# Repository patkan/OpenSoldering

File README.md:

OpenSoldering
=============

###Kurzbeschreibung
OpenSource Lötstation mit (hoffentlich mal) Unterstützung für verschiedene JBC-, Weller- und Ersa-Lötkolben

###Aufbau
Modular. Kommunikation über RS485 mit dem SB9-Bussystem

###Ziel
eine OpenSource Lötstation mit Basisstation und einzelnen Satellitenstationen, die jeweils ein Lötgerät (Kolben, Zange, Pinzette) ansteuern. Auch geeignet für Gruppen oder Werkstätten, die mehrere Lötplätze brauchen.

###Status Quo
- Modul für den JBC-Lötkolben T245A in Entwicklung.
- Thermospannung im Arbeitspunkt für C245 Kartusche 4,2mV; Aufnahme der Kennlinie fehlt noch.

###TODOs
- Aufbau und ausführliche Tests am Lötkolben, Programmierung der PI-Regelung mit Vorsteuerung, (vermutlich kein PID-Konzept nötig) und Bau der Kontrollstation.
- Planung für ein Weller-Modul für die modernen Lötspitzen des WXMP-Lötkolbens, die einen einfachen und günstigen Lötkolben versprechen.
- Planung der Kontrollstation:
	* Display: OLED? gLCD?
	* Eingabe: Drehknopf? Touchscreen?
	* zusätzliche Konnektivität: IoT? Bluetooth? Lötrauchabsaugung?
	* Reglerprofile: Optimierung auf Ausregelzeit/minimale Überschwingung?

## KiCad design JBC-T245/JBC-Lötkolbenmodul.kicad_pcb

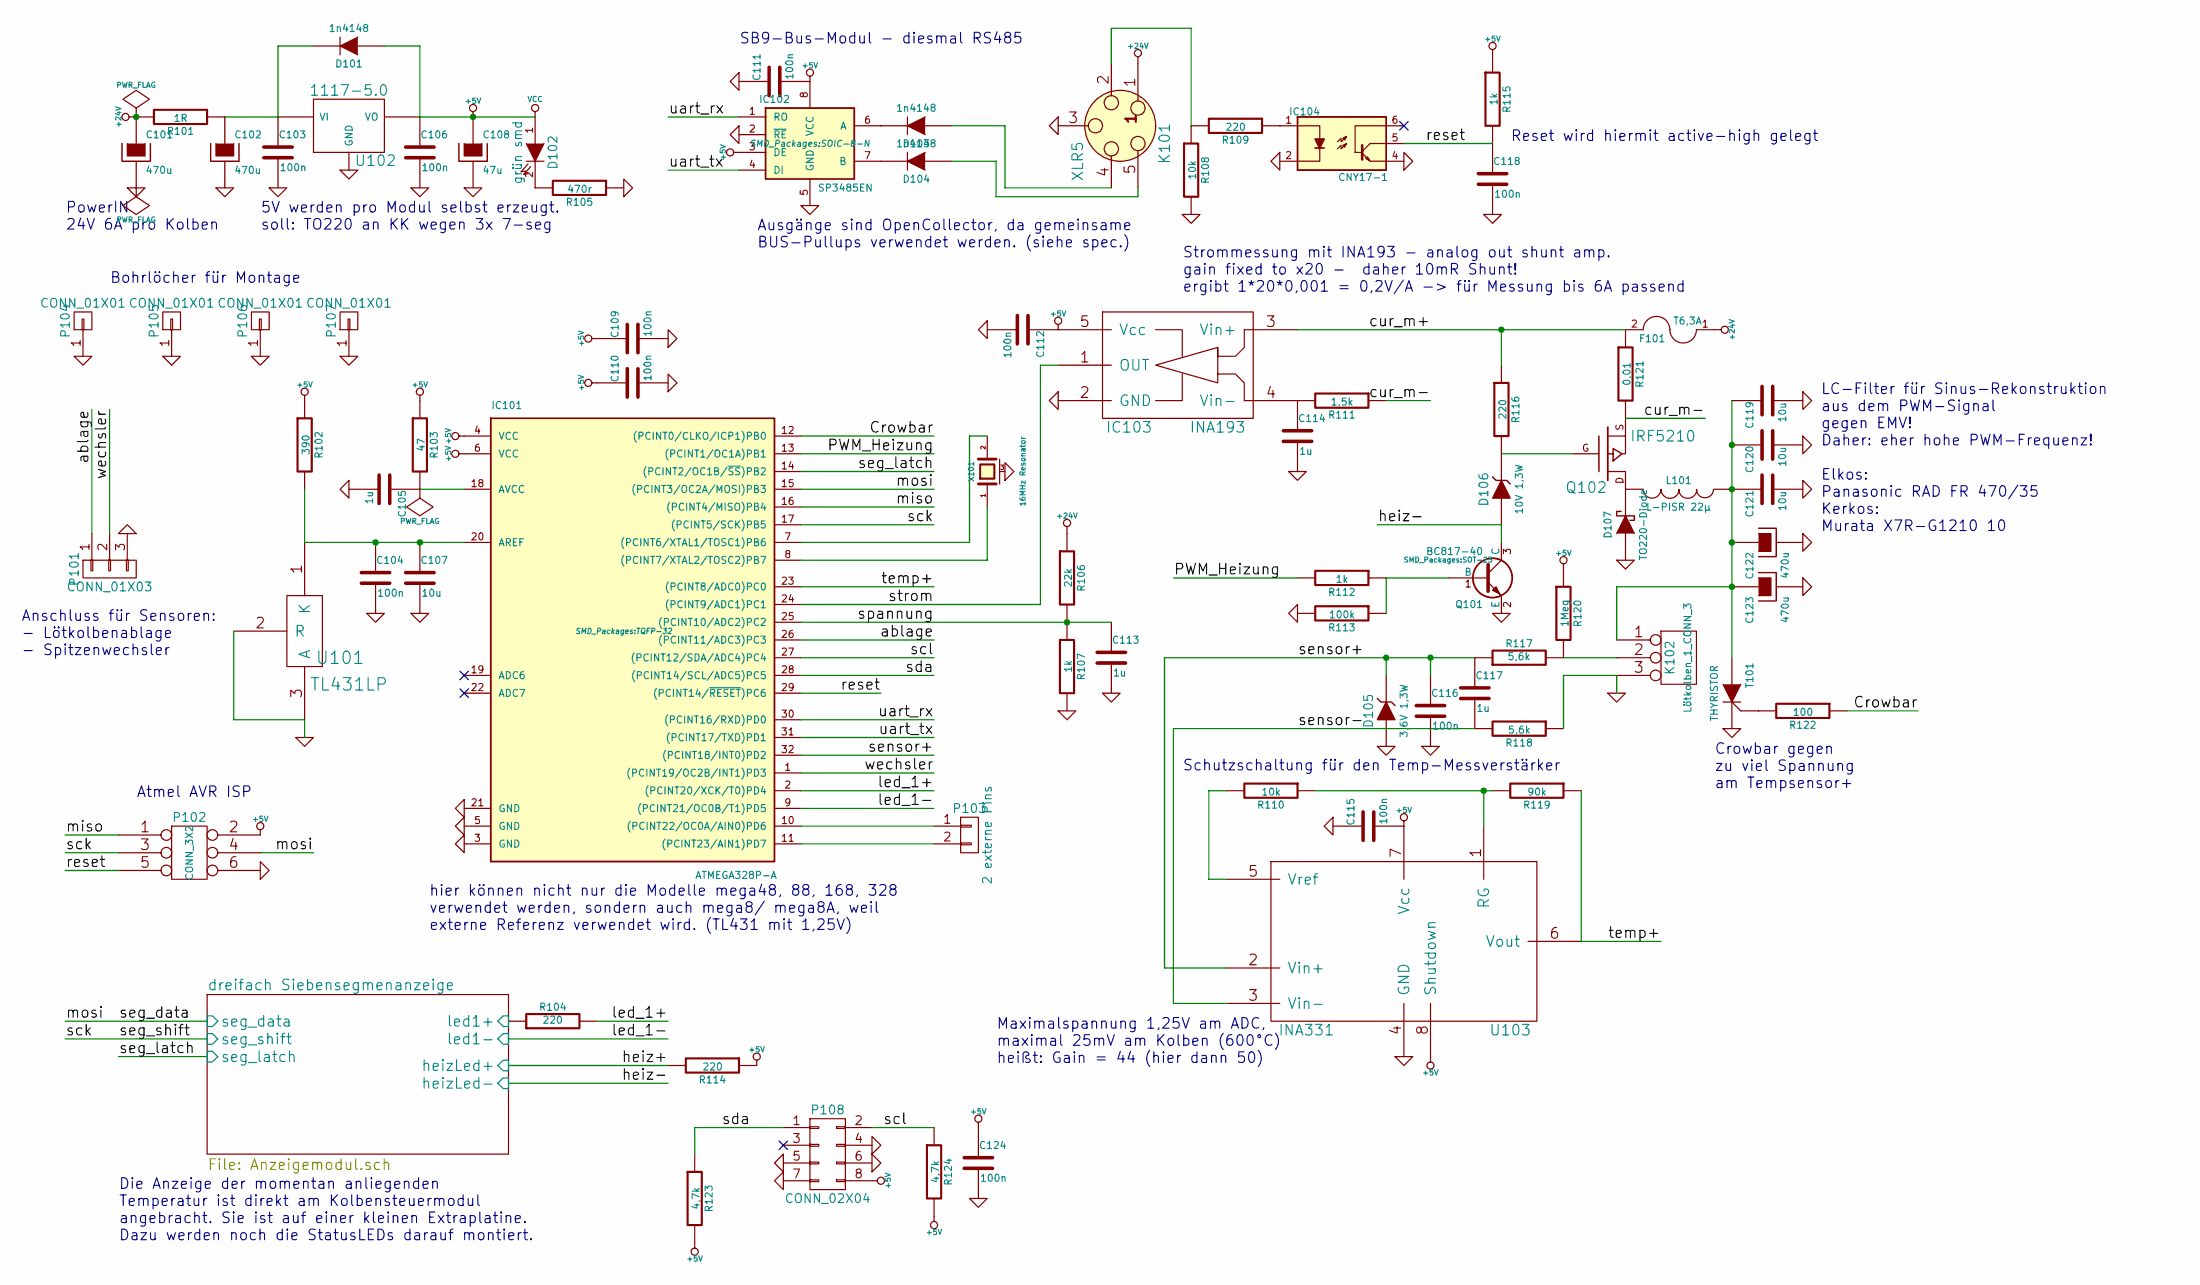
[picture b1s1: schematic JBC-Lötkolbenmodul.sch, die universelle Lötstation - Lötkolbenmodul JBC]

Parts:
C101, C102, C122, C123: 470u; Elko_vert_DM8_RM3-5_CopperClear
C103, C104, C106, C109, C110, C111, C112, C115, C116, C118, C124: 100n; C_0805
C105, C113, C114, C117: 1u; C_0805
C107: 10u; C_0805
C108: 47u; C_1210
C119, C120, C121: 10u; C_1210
D101, D103, D104: 1n4148; Diode-MiniMELF_Standard
D102: grün smd; LED-0805
D105: 3,6V 1,3W; Diode_DO-41_SOD81_Horizontal_RM10
D106: 10V 1,3W; Diode_DO-41_SOD81_Horizontal_RM10
D107: TO220-Diode; TO-220_Neutral123_Vertical
F101: T6,3A; Fuseholder5x20_Horizontal_closed_Bulgin_FX0457
IC101: ATMEGA328P-A; TQFP-32
IC102: SP3485EN; SOIC-8-N
IC103: INA193; SOT-23-5
IC104: CNY17-1; DIP-6__300_ELL
K101: XLR5; Pin_Header_Straight_1x05
K102: Lötkolben_1_CONN_3; Pin_Header_Straight_1x03
L101: L-PISR 22µ; L_Fastron_PISR
P101: CONN_01X03; Pin_Header_Straight_1x03
P102: CONN_3X2; Pin_Header_Straight_2x03
P103: 2 externe Pins; Pin_Header_Straight_1x02
P104, P105, P106, P107: CONN_01X01; 1pin
P108: CONN_02X04; SOIC-8-N
Q101: BC817-40; SOT-23
Q102: IRF5210; DPAK-3_GDS
R101: 1R; R_0603
R102: 390; R_0603
R103: 47; R_0603
R104, R109, R114, R116: 220; R_0603
R105: 470r; R_0603
R106: 22k; R_0603
R107, R112, R115: 1k; R_0603
R108, R110: 10k; R_0603
R111: 1,5k; R_0603
R113: 100k; R_0603
R117, R118: 5,6k; R_0603
R119: 90k; R_0603
R120: 1Meg; R_0603
R121: 0,01; R_1210
R122: 100; R_0603
R123, R124: 4,7k; R_0603
T101: THYRISTOR; TO-220_Neutral123_Vertical
U101: TL431LP; SOIC-8-N
U102: 1117-5.0; TO-220_Neutral123_Vertical
U103: INA331; SSOP-8
X101: 16MHz Resonator; CerOsc_3,2x1,3

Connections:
+24V: C101.1, F101.1, K101.1, R101.2, R106.1
/Crowbar: IC101.12 ((PCINT0/CLKO/ICP1)PB0), R122.1
/PWM_Heizung: IC101.13 ((PCINT1/OC1A)PB1), R112.2
/ablage: IC101.26 ((PCINT11/ADC3)PC3), P101.1
/cur_m+: F101.2, IC103.3 (Vin+), R116.1, R121.1
/cur_m-: Q102.S, R111.1, R121.2
/dreifach Siebensegmenanzeige/heizLed+: R114.2; also elsewhere on the board
/dreifach Siebensegmenanzeige/heizLed-: D106.1 (A), Q101.3 (C); also elsewhere on the board
/dreifach Siebensegmenanzeige/led1+: R104.1; also elsewhere on the board
/dreifach Siebensegmenanzeige/led1-: IC101.9 ((PCINT21/OC0B/T1)PD5); also elsewhere on the board
/dreifach Siebensegmenanzeige/seg_data: IC101.15 ((PCINT3/OC2A/MOSI)PB3), P102.4; also elsewhere on the board
/dreifach Siebensegmenanzeige/seg_latch: IC101.14 ((PCINT2/OC1B/~SS~)PB2); also elsewhere on the board
/dreifach Siebensegmenanzeige/seg_shift: IC101.17 ((PCINT5/SCK)PB5), P102.3; also elsewhere on the board
/led_1+: IC101.2 ((PCINT20/XCK/T0)PD4), R104.2
/miso: IC101.16 ((PCINT4/MISO)PB4), P102.1
/reset: C118.1, IC101.29 ((PCINT14/~RESET~)PC6), IC104.5, P102.5, R115.2
/scl: IC101.27 ((PCINT12/SDA/ADC4)PC4), P108.2, R124.1
/sda: IC101.28 ((PCINT14/SCL/ADC5)PC5), P108.1, R123.1
/sensor+: C116.1, C117.1, D105.2 (K), IC101.32 ((PCINT18/INT0)PD2), R117.1, U103.2 (Vin+)
/sensor-: C117.2, R118.2, U103.3 (Vin-)
/spannung: C113.1, IC101.25 ((PCINT10/ADC2)PC2), R106.2, R107.1
/strom: IC101.24 ((PCINT9/ADC1)PC1), IC103.1 (OUT)
/temp+: IC101.23 ((PCINT8/ADC0)PC0), R119.1, U103.6 (Vout)
/uart_rx: IC101.30 ((PCINT16/RXD)PD0), IC102.1 (RO)
/uart_tx: IC101.31 ((PCINT17/TXD)PD1), IC102.4 (DI)
/wechsler: IC101.1 ((PCINT19/OC2B/INT1)PD3), P101.2
unnamed: C102.1, C103.1, D101.2 (K), R101.1, U102.VI
unnamed: C104.1, C107.1, IC101.20 (AREF), R102.2, U101.1 (K)
unnamed: C105.1, IC101.18 (AVCC), R103.2
unnamed: C114.1, IC103.4 (Vin-), R111.2
unnamed: C119.1, C120.1, C121.1, C122.1, C123.1, K102.1, L101.1, T101.A
unnamed: D102.2 (K), R105.2
unnamed: D103.1 (A), K101.4 (P3)
unnamed: D103.2 (K), IC102.6 (A)
unnamed: D104.1 (A), K101.5
unnamed: D104.2 (K), IC102.7 (B)
unnamed: D106.2 (K), Q102.G, R116.2
unnamed: D107.2 (K), L101.2, Q102.D
unnamed: IC101.7 ((PCINT6/XTAL1/TOSC1)PB6), X101.2
unnamed: IC101.8 ((PCINT7/XTAL2/TOSC2)PB7), X101.1
unnamed: IC101.10 ((PCINT22/OC0A/AIN0)PD6), P103.1
unnamed: IC101.11 ((PCINT23/AIN1)PD7), P103.2
unnamed: IC104.1, R109.1
unnamed: K101.2, R108.1, R109.2
unnamed: K102.2 (PM), R117.2, R120.2
unnamed: Q101.1 (B), R112.1, R113.1
unnamed: R110.1, R119.2, U103.1 (RG)
unnamed: R110.2, U103.5 (Vref)
unnamed: R122.2, T101.G

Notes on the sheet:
Atmel AVR ISP
PowerIN 24V 6A pro Kolben
Crowbar gegen zu viel Spannung am Tempsensor+
Schutzschaltung für den Temp-Messverstärker
SB9-Bus-Modul - diesmal RS485
Ausgänge sind OpenCollector, da gemeinsame BUS-Pullups verwendet werden. (siehe spec.)
5V werden pro Modul selbst erzeugt. soll: TO220 an KK wegen 3x 7-seg
Anschluss für Sensoren: - Lötkolbenablage - Spitzenwechsler
LC-Filter für Sinus-Rekonstruktion aus dem PWM-Signal gegen EMV! Daher: eher hohe PWM-Frequenz! Elkos: Panasonic RAD FR 470/35 Kerkos: Murata X7R-G1210 10
Strommessung mit INA193 - analog out shunt amp. gain fixed to x20 - daher 10mR Shunt! ergibt 1*20*0,001 = 0,2V/A -> für Messung bis 6A passend
Die Anzeige der momentan anliegenden Temperatur ist direkt am Kolbensteuermodul angebracht. Sie ist auf einer kleinen Extraplatine. Dazu werden noch die StatusLEDs darauf montiert.
Maximalspannung 1,25V am ADC, maximal 25mV am Kolben (600°C) heißt: Gain = 44 (hier dann 50)
Reset wird hiermit active-high gelegt
hier können nicht nur die Modelle mega48, 88, 168, 328 verwendet werden, sondern auch mega8/ mega8A, weil externe Referenz verwendet wird. (TL431 mit 1,25V)
Bohrlöcher für Montage

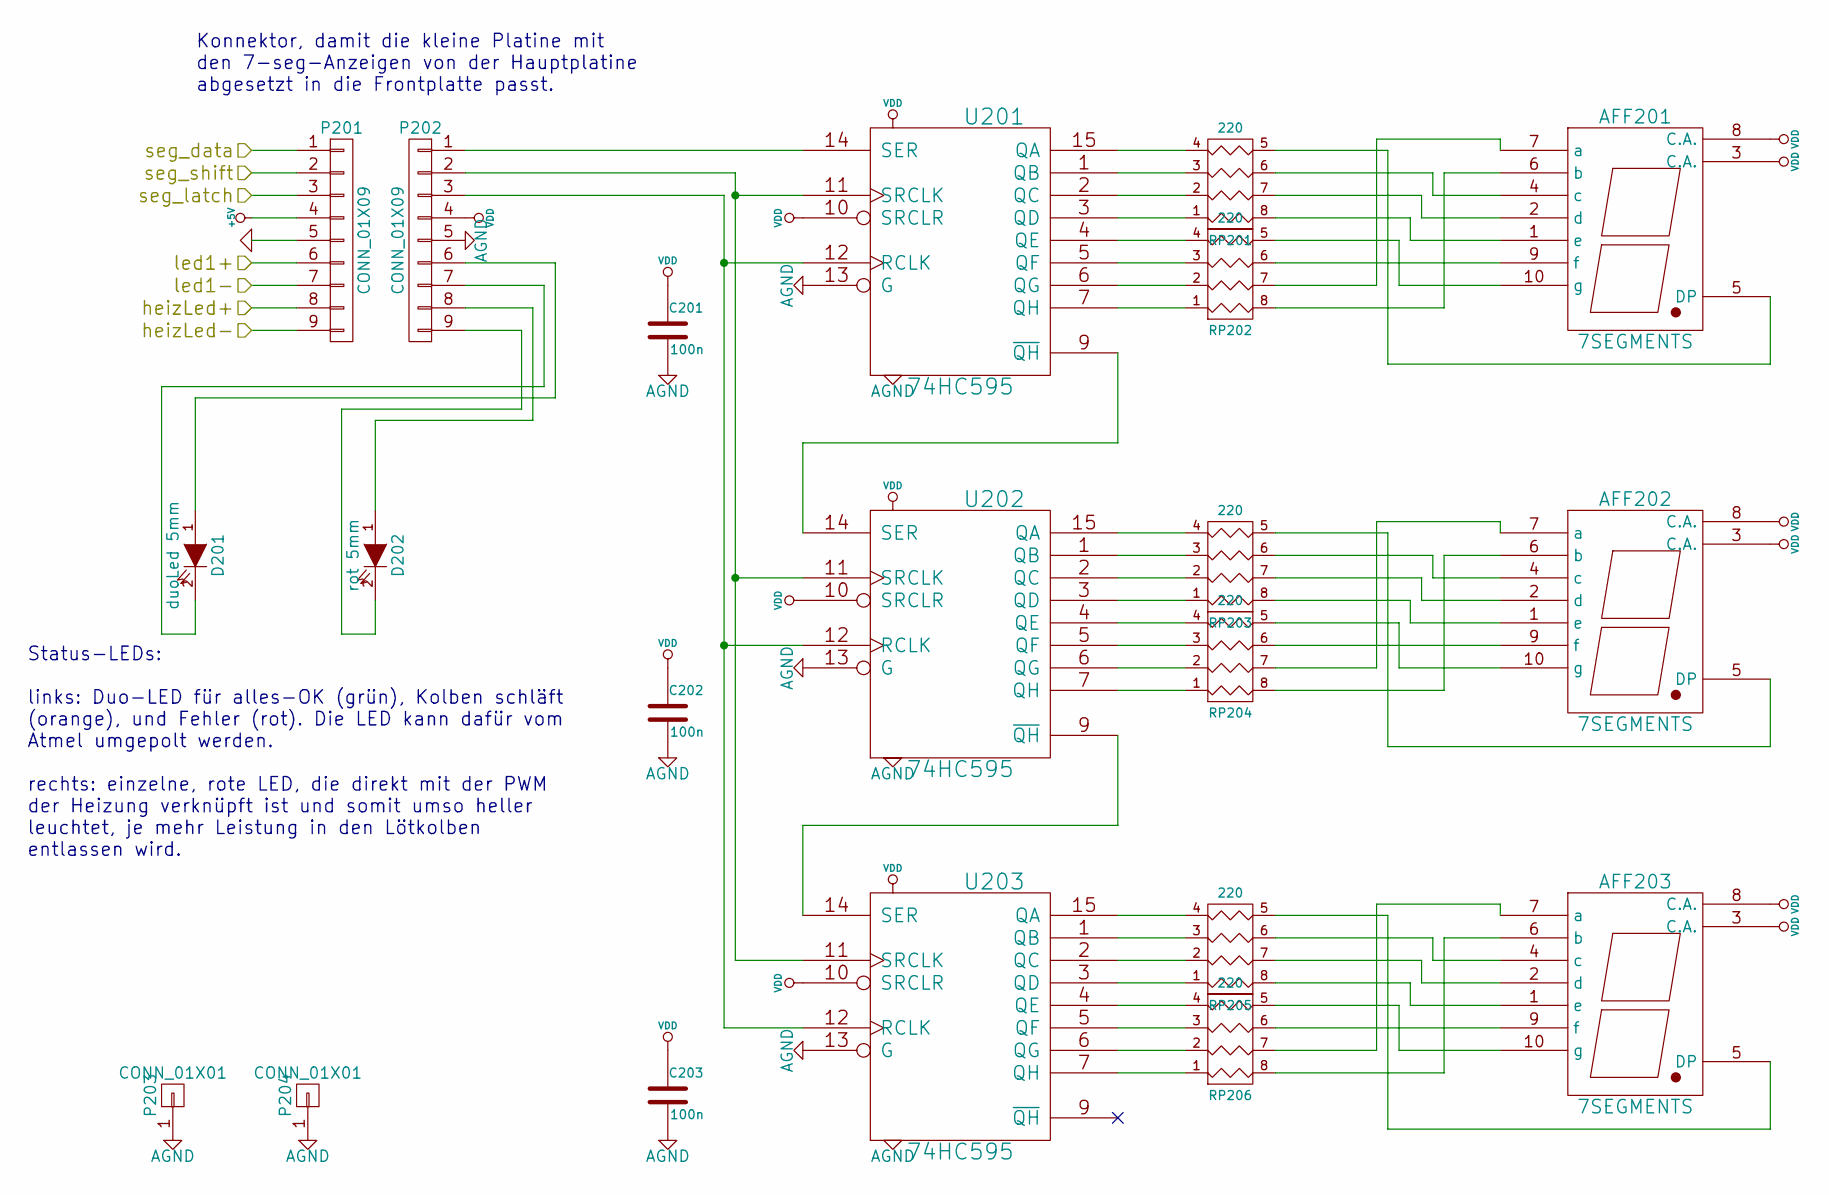
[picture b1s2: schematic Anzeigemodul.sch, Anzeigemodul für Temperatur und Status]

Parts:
AFF201, AFF202, AFF203: 7SEGMENTS; DIP-10__300_ELL
C201, C202, C203: 100n; C_0805
D201: duoLed 5mm; LED-5MM
D202: rot 5mm; LED-5MM
P201: CONN_01X09; Pin_Header_Straight_1x09
P202: CONN_01X09; Pin_Header_Angled_1x09
P203, P204: CONN_01X01; 1pin
RP201, RP202, RP203, RP204, RP205, RP206: 220; R_Cat16-4
U201, U202, U203: 74HC595; SO-16-N

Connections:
/dreifach Siebensegmenanzeige/heizLed+: P201.8; also elsewhere on the board
/dreifach Siebensegmenanzeige/heizLed-: P201.9; also elsewhere on the board
/dreifach Siebensegmenanzeige/led1+: P201.6; also elsewhere on the board
/dreifach Siebensegmenanzeige/led1-: P201.7; also elsewhere on the board
/dreifach Siebensegmenanzeige/seg_data: P201.1; also elsewhere on the board
/dreifach Siebensegmenanzeige/seg_latch: P201.3; also elsewhere on the board
/dreifach Siebensegmenanzeige/seg_shift: P201.2; also elsewhere on the board
unnamed: AFF201.1 (e), RP201.8 (R1)
unnamed: AFF201.2 (d), RP201.7 (R2)
unnamed: AFF201.4 (c), RP201.6 (R3)
unnamed: AFF201.5 (DP), RP201.5 (R4)
unnamed: AFF201.6 (b), RP202.8 (R1)
unnamed: AFF201.7 (a), RP202.7 (R2)
unnamed: AFF201.9 (f), RP202.6 (R3)
unnamed: AFF201.10 (g), RP202.5 (R4)
unnamed: AFF202.1 (e), RP203.8 (R1)
unnamed: AFF202.2 (d), RP203.7 (R2)
unnamed: AFF202.4 (c), RP203.6 (R3)
unnamed: AFF202.5 (DP), RP203.5 (R4)
unnamed: AFF202.6 (b), RP204.8 (R1)
unnamed: AFF202.7 (a), RP204.7 (R2)
unnamed: AFF202.9 (f), RP204.6 (R3)
unnamed: AFF202.10 (g), RP204.5 (R4)
unnamed: AFF203.1 (e), RP205.8 (R1)
unnamed: AFF203.2 (d), RP205.7 (R2)
unnamed: AFF203.4 (c), RP205.6 (R3)
unnamed: AFF203.5 (DP), RP205.5 (R4)
unnamed: AFF203.6 (b), RP206.8 (R1)
unnamed: AFF203.7 (a), RP206.7 (R2)
unnamed: AFF203.9 (f), RP206.6 (R3)
unnamed: AFF203.10 (g), RP206.5 (R4)
unnamed: D201.1 (A), P202.6
unnamed: D201.2 (K), P202.7
unnamed: D202.1 (A), P202.8
unnamed: D202.2 (K), P202.9
unnamed: P202.1, U201.14 (SER)
unnamed: P202.2, U201.11 (SRCLK), U202.11 (SRCLK), U203.11 (SRCLK)
unnamed: P202.3, U201.12 (RCLK), U202.12 (RCLK), U203.12 (RCLK)
unnamed: RP201.1, U201.3 (QD)
unnamed: RP201.2, U201.2 (QC)
unnamed: RP201.3, U201.1 (QB)
unnamed: RP201.4, U201.15 (QA)
unnamed: RP202.1, U201.7 (QH)
unnamed: RP202.2, U201.6 (QG)
unnamed: RP202.3, U201.5 (QF)
unnamed: RP202.4, U201.4 (QE)
unnamed: RP203.1, U202.3 (QD)
unnamed: RP203.2, U202.2 (QC)
unnamed: RP203.3, U202.1 (QB)
unnamed: RP203.4, U202.15 (QA)
unnamed: RP204.1, U202.7 (QH)
unnamed: RP204.2, U202.6 (QG)
unnamed: RP204.3, U202.5 (QF)
unnamed: RP204.4, U202.4 (QE)
unnamed: RP205.1, U203.3 (QD)
unnamed: RP205.2, U203.2 (QC)
unnamed: RP205.3, U203.1 (QB)
unnamed: RP205.4, U203.15 (QA)
unnamed: RP206.1, U203.7 (QH)
unnamed: RP206.2, U203.6 (QG)
unnamed: RP206.3, U203.5 (QF)
unnamed: RP206.4, U203.4 (QE)
unnamed: U201.9 (~QH), U202.14 (SER)
unnamed: U202.9 (~QH), U203.14 (SER)

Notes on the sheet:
Konnektor, damit die kleine Platine mit den 7-seg-Anzeigen von der Hauptplatine abgesetzt in die Frontplatte passt.
Status-LEDs: links: Duo-LED für alles-OK (grün), Kolben schläft (orange), und Fehler (rot). Die LED kann dafür vom Atmel umgepolt werden. rechts: einzelne, rote LED, die direkt mit der PWM der Heizung verknüpft ist und somit umso heller leuchtet, je mehr Leistung in den Lötkolben entlassen wird.

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
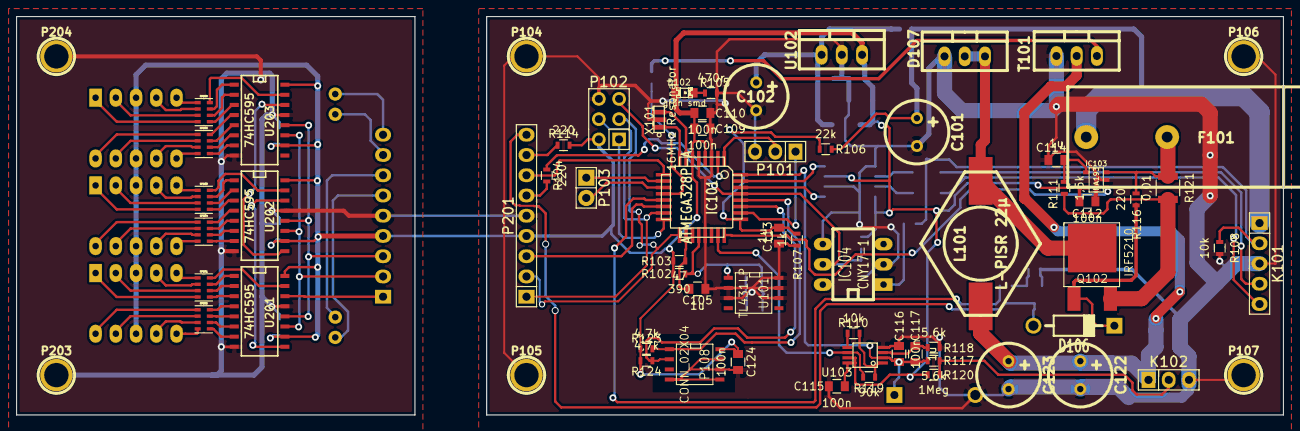
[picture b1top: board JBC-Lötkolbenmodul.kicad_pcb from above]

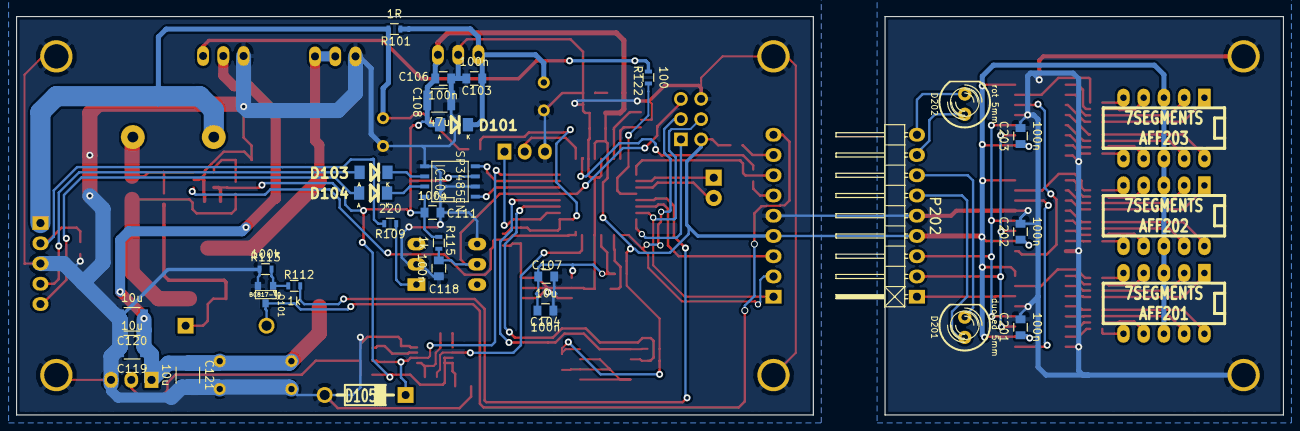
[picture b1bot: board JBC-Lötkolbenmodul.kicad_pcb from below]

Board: 2 copper layers, 159.0 x 50.0 mm, 99 parts (31 on the bottom side), 108 nets.

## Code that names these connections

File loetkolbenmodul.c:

/*
 *    Filename: loetkobenmodul.c
 *     Version: 0.0.4
 * Description: Ansteuerung eines JBC T245A Lötkolbens
 *     License: GPLv3 or later
 *     Depends: global.h, io.h, interrupt.h, sb9, i2c
 *
 *      Author: Copyright (C) Philipp Hörauf
 *        Date: 2014-12-19
 *
 *  This program is free software; you can redistribute it and/or modify
 *  it under the terms of the GNU General Public License as published by
 *  the Free Software Foundation; either version 2 of the License, or
 *  (at your option) any later version.
 *
 *  This program is distributed in the hope that it will be useful,
 *  but WITHOUT ANY WARRANTY; without even the implied warranty of
 *  MERCHANTABILITY or FITNESS FOR A PARTICULAR PURPOSE.  See the
 *  GNU General Public License for more details.
 *
 *  You should have received a copy of the GNU General Public License
 *  along with this program; if not, write to the Free Software
 *  Foundation, Inc., 59 Temple Place, Suite 330, Boston, MA  02111-1307  USA
 *
 */

#include "definitionen.h"
#include "pid.c"
extern volatile float kp, ki, kd; //TODO --> das hier soll noch weg


void setKolbenPower (float sollwert) {
	// 16bit Timer1 auf FastPWM, Ausgang OC1A sei Lötkolben.
}

// Der ADC wird interruptgesteuert
volatile uint8_t counter = 0; // für Berechnung von Heizleistung und Temperatur des Lötkolbens
volatile float leistung = 0, rawtemp = 0, spitzentemp = 0;
volatile uint16_t heizstrom = 0, eingangsspannung = 0; // U in mV, I in mA
volatile uint16_t solltemperatur = 0, platinentemperatur = 0;

//volatile float ki = 1, kp = 1, kd = 1; // werden bereits in pid.c deklariert --> Zugriff sollte am besten nur über setTunings erfolgen

ISR (TIMER0_OVF_vect, ISR_BLOCK) {
	ADMUX = ADMUX & 0b11100000; // lösche selektiv die MUX-Bits
	ADMUX |= (counter%3); // setze ADC-Kanal neu
	ADCSRA |= 1<<ADSC; // start conversion

	// Auslesung der Temperatur des LM75-Sensors
	static uint8_t i2cAuslesung = 0;
	if (i2cAuslesung == 123) { // es sind ca 500 ms vergangen
		platinentemperatur = (i2cRxLm75 (0b1001000)) /16; // erst mal in ganzen °C
		i2cAuslesung = 0;
	} else {
		i2cAuslesung++;
	}


	// PID Regler muss auch hier drin arbeiten, da er mit gleichem Zeitabstand
	// ausgeführt wird, wie der ADC. bzw. mit 1/3 der ADC Frequenz.

	/* Erklärung der Ausgangsübertragungsfunktion und der Regelung:
	

	* 
	* yk	= Ausgangswert des Integrators
	* ek	= Differenz der Temperatur vom Sollwert (+ => zu kalt)
	* ki	= I-Verstärungswert
	* kr	= Reglerverstärkung
	* 
	* Eine Vorsteuerung hat wegen der stark wechselnden Lastsituationen
	* keinen großen Sinn und wird daher weggelassen.

	*
	* Die Störung Z(s) wirkt direkt auf die Temperatur der Lötspitze ein, sie
	* ist der Wärmestrom von der Lötspitze in die Luft (Standardfall) oder in
	* die Lötstelle (Regler muss eingreifen)
	*/


	//TODO: dies ist der neue Aufruf für die externe PID-Funktion
	//float yk;
	//yk = pid_compute(spitzentemp, solltemperatur);



	
	// Regler (Konzept: PI)
	float ek = solltemperatur - rawtemp;
	static float yk;
	yk += (ki * ek);
	

	// Weitergabe an Ausgabefunktion:
	setKolbenPower (yk + (kp * ek));
}

// ADC Conversion Complete Interrupt
// ADC0 = Temperatur, ADC1 = Heizstrom, ADC2 = Systemspannung
// Die Werte können noch kalibriert werden, allerdings nicht zur Laufzeit.

#define REFERENZ 1			// externe Referenz, 1250mV also 1,2207mV pro STEP
#define ABWEICHUNG 0.220703125		// gemessene Abweichung in %/100 vom exakten Referenzspannungswert
#define MITTELWERTE 4
#define SPANNUNG_PRO_GRAD 1.00000	// Spannung am ADC pro Grad am Lötkolben
#define SPANNUNG_PRO_AMPERE 0.2		// Spannung am ADC pro Ampere das durch die Heizung fließt
#define SPANNUNG_PRO_VOLT 0.04347826	// Spannung am ADC pro Volt der Versorgungsspannung

ISR (ADC_vect, ISR_BLOCK) {
	// 	uartTxStrln("adc");
	// ADC-Auslesungen und Rechnung mit Gleitmittelwert über 4 Werte
	static uint16_t tabelle[3*MITTELWERTE]; // hier kommen die ADC-werte rein.
	uint16_t temp=0;
	tabelle[counter] = ADC; // fülle Tabelle mit ADC-Werten

// 	TODO: Formeln anpassen!!

	switch (counter%3) {
		case 0:
			// Achtung: die Lötspitze wird kaltstellenkompensiert (daher die Zusatzvariable)
			spitzentemp = spitzentemp*0.95 + (((float)((temp*REFERENZ)<<2)*ABWEICHUNG*SPANNUNG_PRO_GRAD) + platinentemperatur)*0.05;
			rawtemp = ((float)((tabelle[counter]*REFERENZ)<<2)*ABWEICHUNG*SPANNUNG_PRO_GRAD) + platinentemperatur;
			break;

		case 1:
			// Heizstrom wird ausgerechnet
			for(uint8_t i=0; i<MITTELWERTE; i++) {
				temp += tabelle[1 + 3*i];
			}
			heizstrom = (uint16_t)((float)((temp*REFERENZ)<<2)*ABWEICHUNG*SPANNUNG_PRO_AMPERE);
			break;

		case 2:
			// Eingangsspannung wird ausgerechnet
			for(uint8_t i=0; i<MITTELWERTE; i++) {
				temp += tabelle[2 + 3*i];
			}
			eingangsspannung = (uint16_t)((float)temp*ABWEICHUNG*SPANNUNG_PRO_VOLT);
			break;
	}
	counter++;
	if (counter == 3*MITTELWERTE) { // setze Counter zurück
		counter = 0;
	}
	leistung = ((float)heizstrom * (float)eingangsspannung) / 1000; // Leistung in Watt
}



int main(void) {

	// Allgemeine PIN- und PORT-Einstellungen
	DDRB = 1<<PB0 | 1<<PB1 | 1<<PB2 | 1<<PB3 | 1<<PB5;
	DDRD = 1<<PD1 | 1<<PD4 | 1<<PD5; // PD4 ist WS2812B Datenpin
	PORTC = 1<<PC3; // Pullup für Lötkolbenständerschalter
	PORTD = 1<<PD3; // Lötspitzenwechslerschalter

	delayms(100);

	spiInit();
	i2cInit();
	lm75Init();
// 	timerInit();
// 	uartInit();
	writeSegments(42);

	// Initialiserung der WS2812-StatusLED
	struct cRGB led[1];
	led[0].g=128;
	led[0].b=75;
	led[0].b=25;
	ws2812_setleds(led,1);

// 	sei(); // und es seien Interrupts :D


	delayus(10);
	i2cRxLm75Start(0b1001000);

	while(1) {
// 		i2cRxLm75Start(0b1001000);
// 		temp = i2cRxLm75 (0b1001000);
// 		writeSegments (i2cERR & 0xF8);
		writeSegments (platinentemperatur);
		delayms(100);
	}
	return 0;
}

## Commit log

2014-10-26 initial commit - erst mal das Projekt so online gestellt. philippH
2014-11-21 schutz für den Temperaturmesswandler verbessert
2014-12-19 Programm angefangen.
2014-12-20 fehlerhaftes footprint des 16MHz resonators. fixed. programm geht los.
2014-12-20 Planung Controllermodul und Thermospannung C245 Kartusche hinzugefügt.
2014-12-20 programm zählt ein bisschen. LED-anzeigen gehen also.
2014-12-20 gerberfiles in der gitignore datei verzeichnet.
2014-12-20 die Modularisierung zieht ein. inits und definitionen werden aus der main-Datei ausgelagert.
2014-12-20 dateien verschoben, da diese nicht spezifisch für den JBC-kolben sind.
2014-12-21 light_ws2812 hinzugefügt
2014-12-21 anfang hardware i2c für den LM75 Tempsensor
2014-12-21 ws2812 port und Pin korrekt eingestellt. i2c geht noch nicht.
2014-12-21 arbeit an der i2c Kommunikation. noch unfertig
2014-12-21 i2c weiter versuchen :(
2014-12-21 änderungen i2c. noch keine lesefunktion, schreiben geht.
2014-12-21 temperatur des lm75 kann jetzt gelesen werden. leider noch nur 8 bit aber lesen geht schon mal.
2014-12-26 ADC und Timerfunktionen (tlw. aus server_lader übernommen) dazugefügt.
2014-12-26 anfang der regelung
2014-12-27 anfang der Regelung und änderung der ADC-steuerung auf Timer0 wegen nötigkeit des Timer1 für die PWM des Lötkolbens.
2014-12-27 timereinstellungen für timer1 gesetzt.
2014-12-27 Reglerschaubild in DIA dazugefügt
2014-12-28 teilweise Beschreibung der Regelung geschrieben.
2014-12-28 ADC-Auswertung incl. Kaltstellenkompensation dazugefügt. Faktor für Lötspitze muss allerdings noch angepasst werden
2014-12-29 README etwas aufgehübscht
2014-12-31 BREAKS BUILD: loetkolbemodul.c auf pid-Regler vorbereitet
2015-01-06 Regelungsfunktion eingebaut - danke mgmax!
2015-01-07 BUILDS AGAIN; rauliche Startimplementierung eines PID-Controllers; Datentypen sind noch Pfusch
2015-01-18 Variablenkollision aufgeräumt, baut wieder
2015-01-18 aufgeräumt für upstream pull request
